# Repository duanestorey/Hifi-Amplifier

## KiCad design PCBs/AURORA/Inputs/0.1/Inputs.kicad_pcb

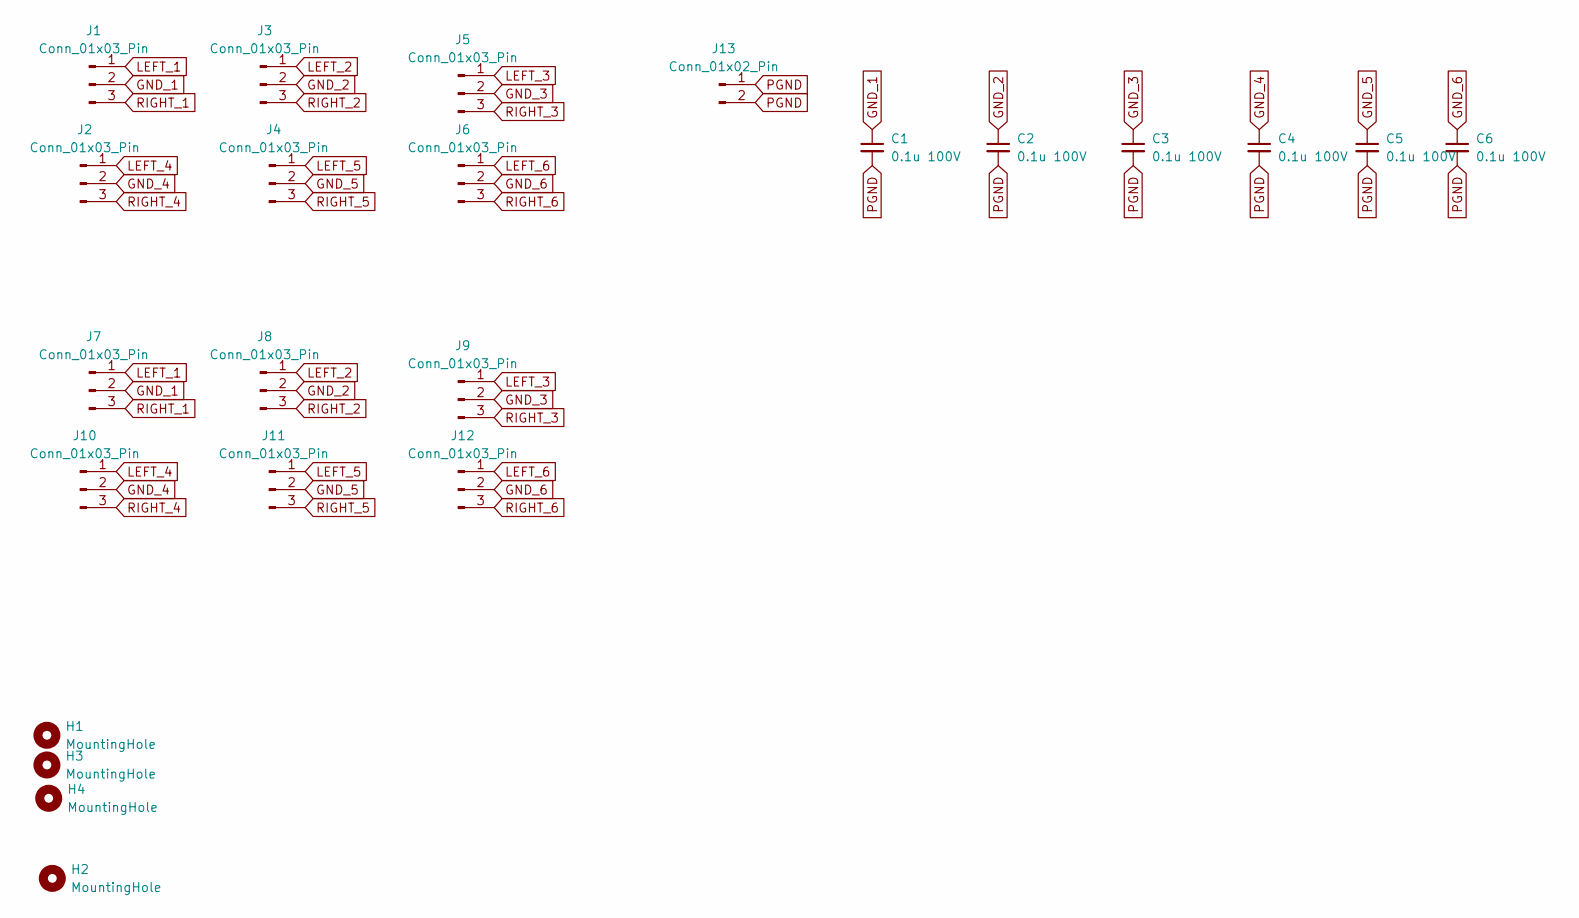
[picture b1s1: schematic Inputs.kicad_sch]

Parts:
C1, C2, C3, C4, C5, C6: 0.1u 100V; C_1206_3216Metric
H1, H2, H3, H4: MountingHole; MountingHole_3.2mm_M3
J1, J2, J3, J4, J5, J6, J7, J8, J9, J10, J11, J12: Conn_01x03_Pin; JST_PH_B3B-PH-K_1x03_P2.00mm_Vertical
J13: Conn_01x02_Pin; JST_VH_B2P-VH-B_1x02_P3.96mm_Vertical

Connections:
GND_1: C1.1, J1.2, J7.2
GND_2: C2.1, J3.2, J8.2
GND_3: C3.1, J5.2, J9.2
GND_4: C4.1, J2.2, J10.2
GND_5: C5.1, J4.2, J11.2
GND_6: C6.1, J6.2, J12.2
LEFT_1: J1.1, J7.1
LEFT_2: J3.1, J8.1
LEFT_3: J5.1, J9.1
LEFT_4: J2.1, J10.1
LEFT_5: J4.1, J11.1
LEFT_6: J6.1, J12.1
PGND: C1.2, C2.2, C3.2, C4.2, C5.2, C6.2, J13.1, J13.2
RIGHT_1: J1.3, J7.3
RIGHT_2: J3.3, J8.3
RIGHT_3: J5.3, J9.3
RIGHT_4: J2.3, J10.3
RIGHT_5: J4.3, J11.3
RIGHT_6: J6.3, J12.3

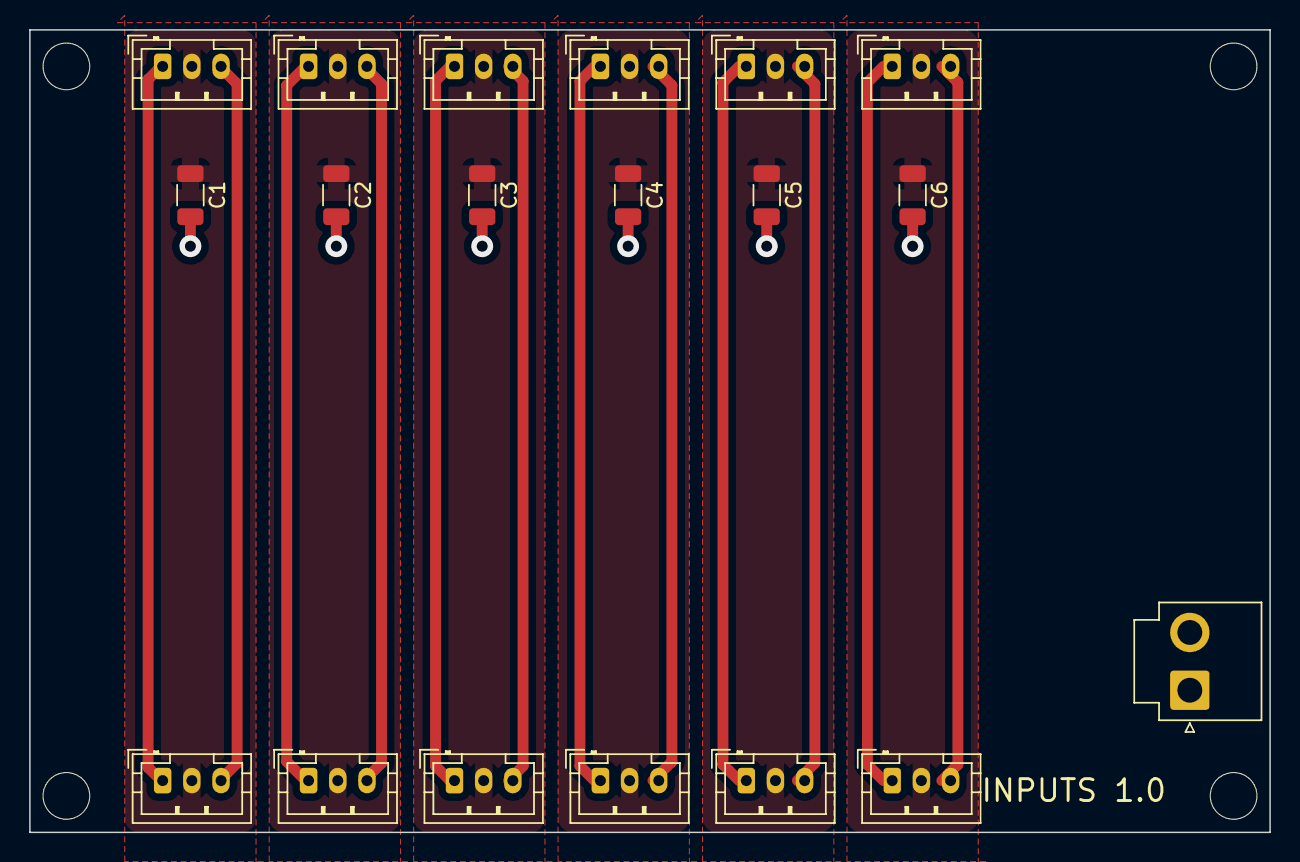
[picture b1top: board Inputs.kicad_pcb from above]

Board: 2 copper layers, 85.0 x 55.0 mm, 23 parts (0 on the bottom side), 19 nets.

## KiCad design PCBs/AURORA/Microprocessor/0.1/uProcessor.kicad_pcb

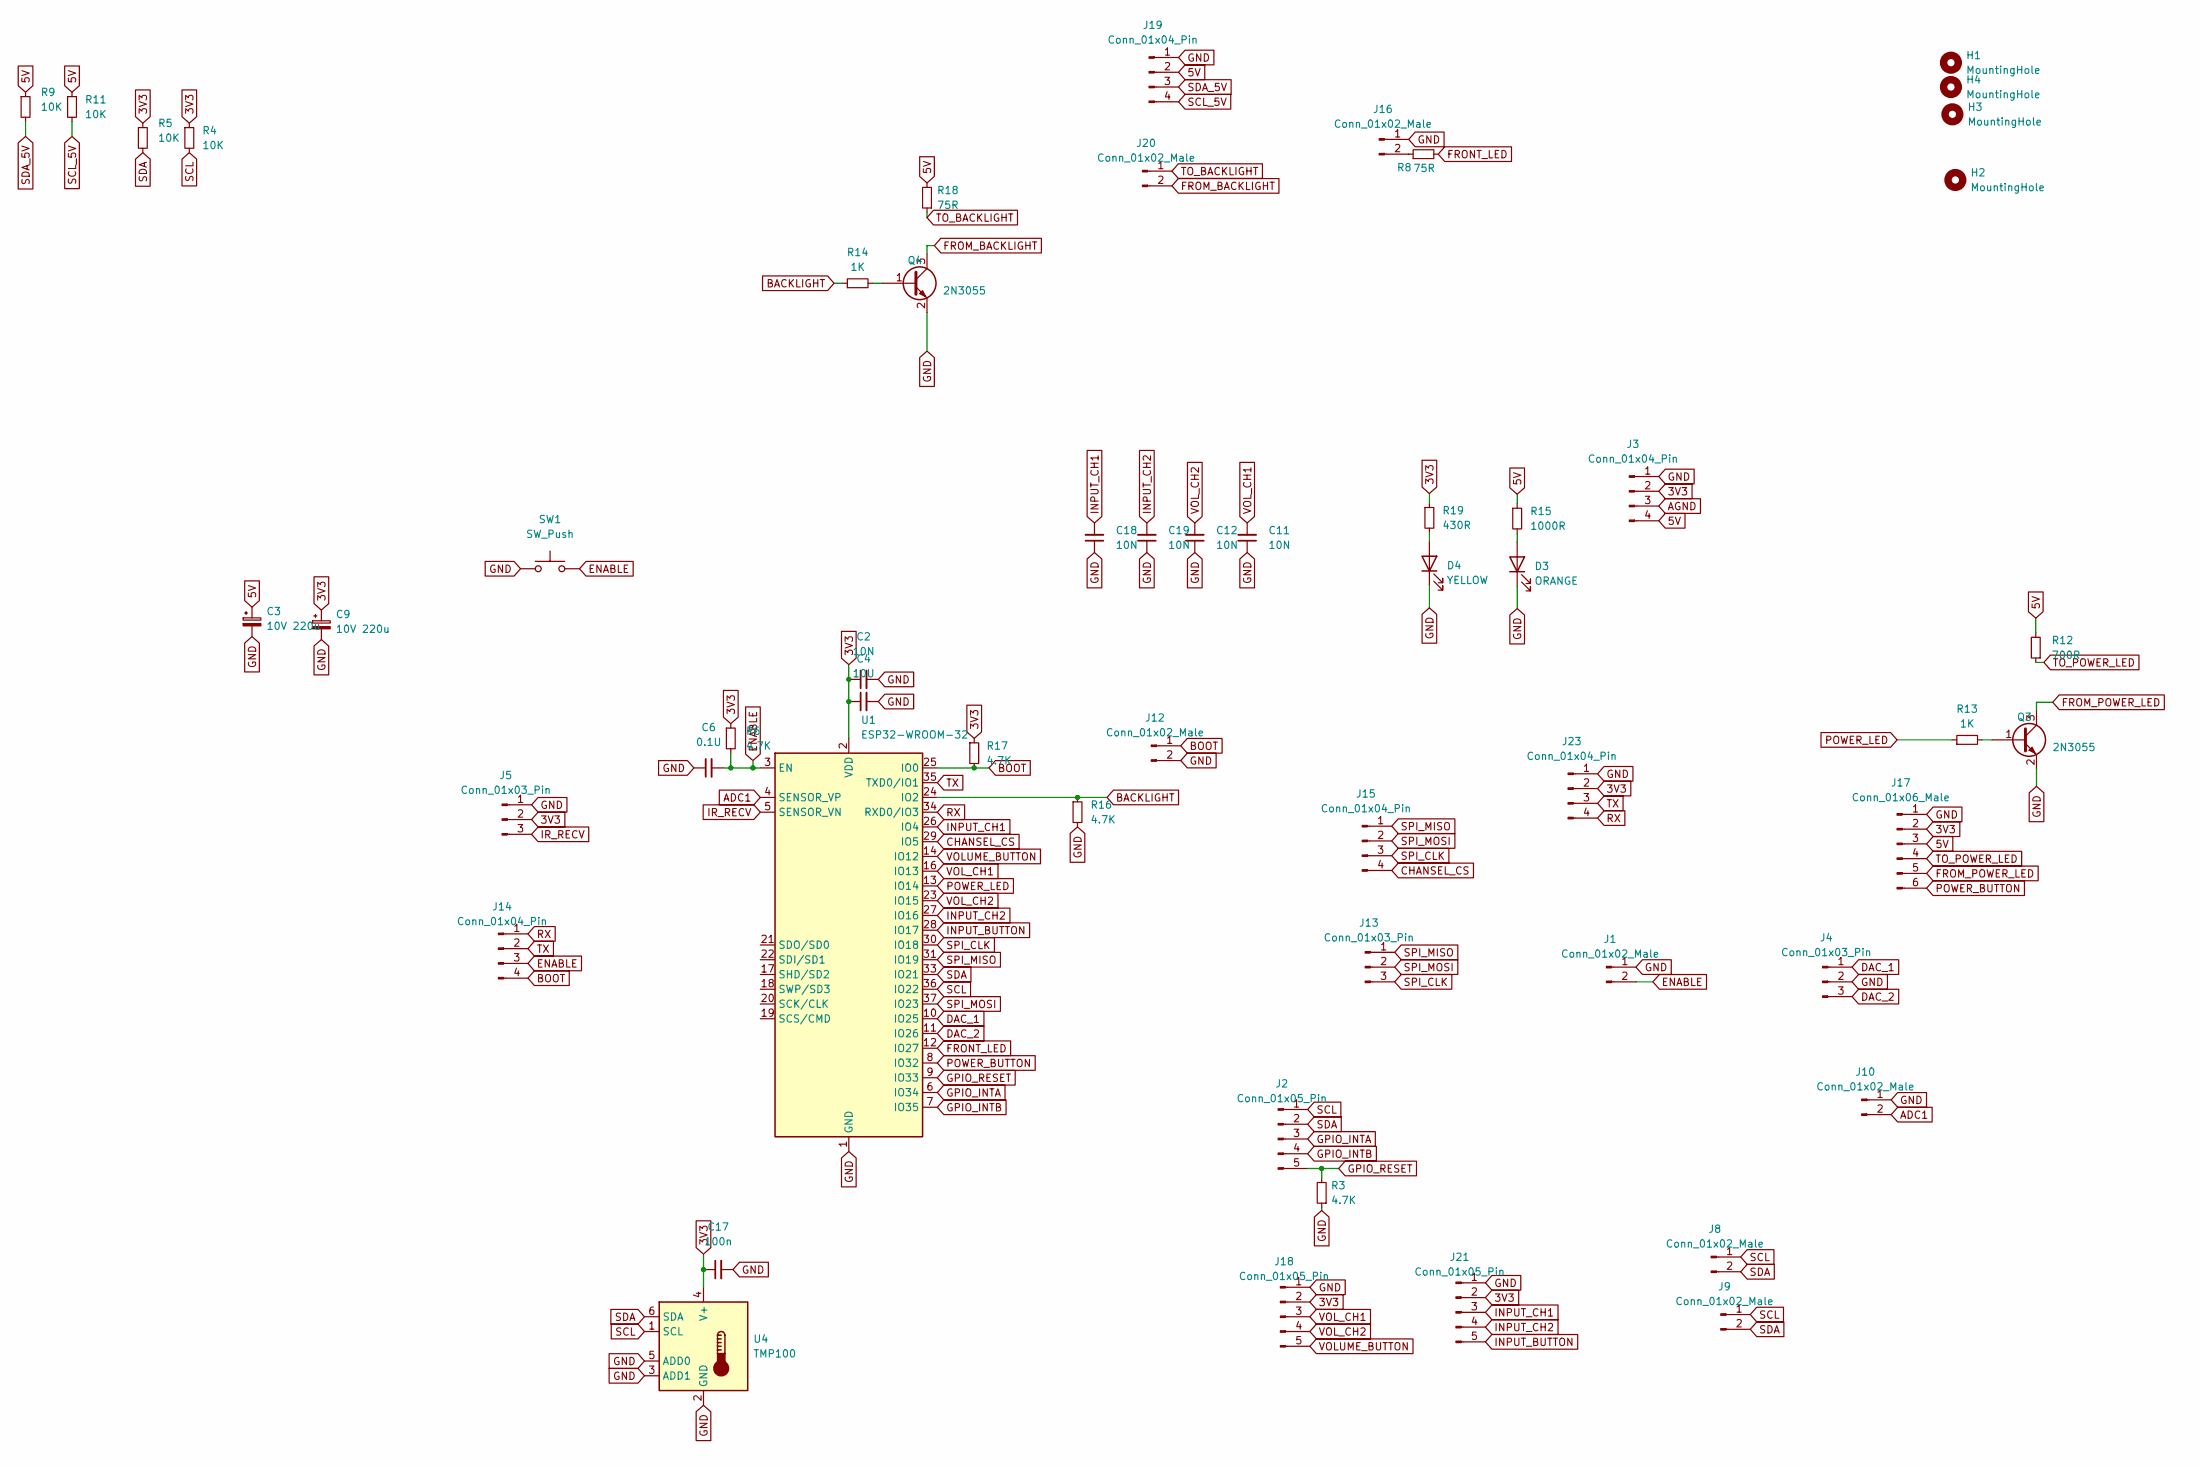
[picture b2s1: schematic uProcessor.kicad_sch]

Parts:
C2: 10N; C_0805_2012Metric_Pad1.18x1.45mm_HandSolder
C3, C9: 10V 220u; CP_Radial_D6.3mm_P2.50mm
C4: 10U; C_1206_3216Metric_Pad1.33x1.80mm_HandSolder
C6: 0.1U; C_0805_2012Metric_Pad1.18x1.45mm_HandSolder
C11, C12, C18, C19: 10N; C_0603_1608Metric_Pad1.08x0.95mm_HandSolder
C17: 100n; C_0805_2012Metric_Pad1.18x1.45mm_HandSolder
D3: ORANGE; LED_0805_2012Metric_Pad1.15x1.40mm_HandSolder; LCSC XL-1608UBC-04
D4: YELLOW; LED_0805_2012Metric_Pad1.15x1.40mm_HandSolder; LCSC NCD0603R1
H1, H2, H3, H4: MountingHole; MountingHole_3.2mm_M3
J1, J8, J9, J10, J16, J20: Conn_01x02_Male; JST_PH_B2B-PH-K_1x02_P2.00mm_Vertical
J2, J18, J21: Conn_01x05_Pin; JST_PH_B5B-PH-K_1x05_P2.00mm_Vertical
J3, J14, J15, J19: Conn_01x04_Pin; JST_PH_B4B-PH-K_1x04_P2.00mm_Vertical
J4, J5, J13: Conn_01x03_Pin; JST_PH_B3B-PH-K_1x03_P2.00mm_Vertical
J12: Conn_01x02_Male; PinHeader_1x02_P2.54mm_Vertical
J17: Conn_01x06_Male; JST_PH_B6B-PH-K_1x06_P2.00mm_Vertical
J23: Conn_01x04_Pin; PinHeader_1x04_P2.54mm_Vertical
Q3, Q4: 2N3055; TSOT-23
R3, R6, R16, R17: 4.7K; R_0603_1608Metric_Pad0.98x0.95mm_HandSolder
R4, R5, R9, R11: 10K; R_0603_1608Metric_Pad0.98x0.95mm_HandSolder
R8, R18: 75R; R_0603_1608Metric_Pad0.98x0.95mm_HandSolder
R12: 700R; R_0603_1608Metric_Pad0.98x0.95mm_HandSolder
R13, R14: 1K; R_0603_1608Metric_Pad0.98x0.95mm_HandSolder
R15: 1000R; R_0603_1608Metric_Pad0.98x0.95mm_HandSolder
R19: 430R; R_0603_1608Metric_Pad0.98x0.95mm_HandSolder
SW1: SW_Push; Button Aliexpress 4x4
U1: ESP32-WROOM-32; ESP32-WROOM-32E
U4: TMP100; SOT-23-6

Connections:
3V3: C2.1, C4.1, C9.1, C17.1, J3.2, J5.2, J17.2, J18.2, J21.2, J23.2, R4.1, R5.1, R6.1, R17.1, R19.1, U1.2 (VDD), U4.4 (V+)
5V: C3.1, J3.4, J17.3, J19.2, R9.1, R11.1, R12.2, R15.1, R18.2
ADC1: J10.2, U1.4 (SENSOR_VP)
AGND: J3.3
BACKLIGHT: R14.1, R16.1, U1.24 (IO2)
BOOT: J12.1, J14.4, R17.2, U1.25 (IO0)
CHANSEL_CS: J15.4, U1.29 (IO5)
DAC_1: J4.1, U1.10 (IO25)
DAC_2: J4.3, U1.11 (IO26)
ENABLE: C6.2, J1.2, J14.3, R6.2, SW1.2, U1.3 (EN)
FROM_BACKLIGHT: J20.2, Q4.3 (C)
FROM_POWER_LED: J17.5, Q3.3 (C)
FRONT_LED: R8.2, U1.12 (IO27)
GND: C2.2, C3.2, C4.2, C6.1, C9.2, C11.1, C12.1, C17.2, C18.1, C19.1, D3.1 (K), D4.1 (K), J1.1, J3.1, J4.2, J5.1, J10.1, J12.2, J16.1, J17.1, J18.1, J19.1, J21.1, J23.1, Q3.2 (E), Q4.2 (E), R3.1, R16.2, SW1.1, U1.1 (GND), U1.15 (GND), U1.38 (GND), U1.39 (GND), U4.2 (GND), U4.3 (ADD1), U4.5 (ADD0)
GPIO_INTA: J2.3, U1.6 (IO34)
GPIO_INTB: J2.4, U1.7 (IO35)
GPIO_RESET: J2.5, R3.2, U1.9 (IO33)
INPUT_BUTTON: J21.5, U1.28 (IO17)
INPUT_CH1: C18.2, J21.3, U1.26 (IO4)
INPUT_CH2: C19.2, J21.4, U1.27 (IO16)
IR_RECV: J5.3, U1.5 (SENSOR_VN)
unnamed: D3.2 (A), R15.2
unnamed: D4.2 (A), R19.2
unnamed: J16.2, R8.1
unnamed: Q3.1 (B), R13.2
unnamed: Q4.1 (B), R14.2
POWER_BUTTON: J17.6, U1.8 (IO32)
POWER_LED: R13.1, U1.13 (IO14)
RX: J14.1, J23.4, U1.34 (RXD0/IO3)
SCL: J2.1, J8.1, J9.1, R4.2, U1.36 (IO22), U4.1 (SCL)
SCL_5V: J19.4, R11.2
SDA: J2.2, J8.2, J9.2, R5.2, U1.33 (IO21), U4.6 (SDA)
SDA_5V: J19.3, R9.2
SPI_CLK: J13.3, J15.3, U1.30 (IO18)
SPI_MISO: J13.1, J15.1, U1.31 (IO19)
SPI_MOSI: J13.2, J15.2, U1.37 (IO23)
TO_BACKLIGHT: J20.1, R18.1
TO_POWER_LED: J17.4, R12.1
TX: J14.2, J23.3, U1.35 (TXD0/IO1)
VOLUME_BUTTON: J18.5, U1.14 (IO12)
VOL_CH1: C11.2, J18.3, U1.16 (IO13)
VOL_CH2: C12.2, J18.4, U1.23 (IO15)

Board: 2 copper layers, 55 parts (0 on the bottom side), 41 nets, no tracks yet.

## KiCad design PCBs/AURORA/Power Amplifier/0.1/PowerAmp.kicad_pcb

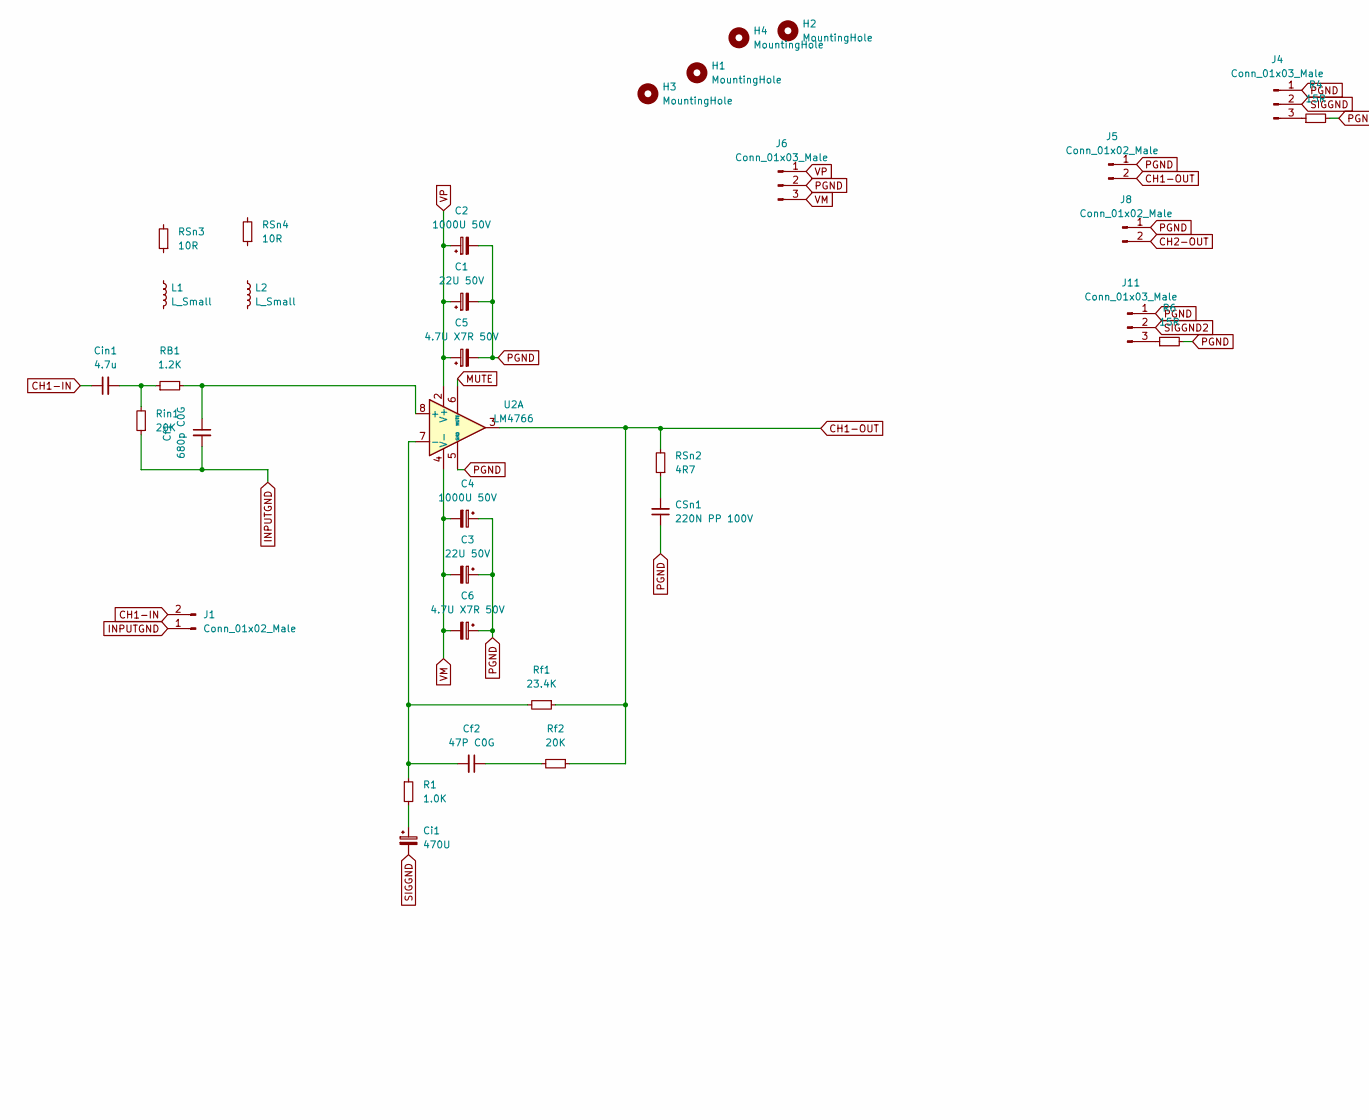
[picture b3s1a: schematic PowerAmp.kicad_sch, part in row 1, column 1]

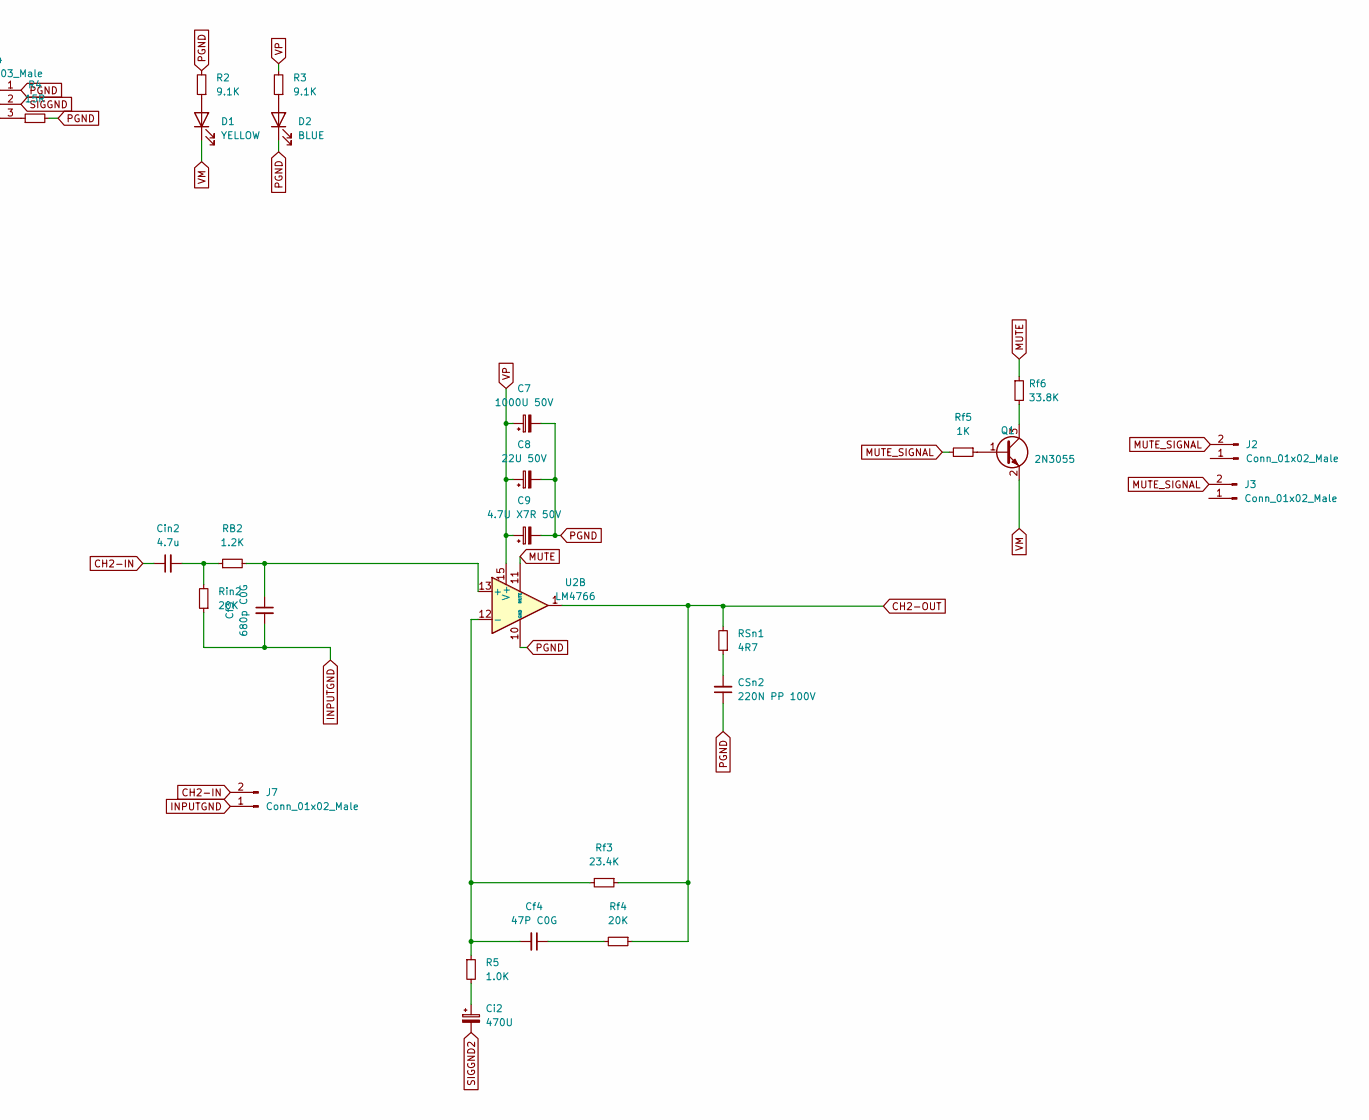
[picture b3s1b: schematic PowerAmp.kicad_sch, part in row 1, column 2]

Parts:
C1, C3, C8: 22U 50V; CP_Radial_D6.3mm_P2.50mm
C2, C4, C7: 1000U 50V; CP_Radial_D12.5mm_P5.00mm
C5, C6, C9: 4.7U X7R 50V; C_1206_3216Metric_Pad1.33x1.80mm_HandSolder
CSn1, CSn2: 220N PP 100V; C_Rect_L18.0mm_W7.0mm_P15.00mm_FKS3_FKP3
Cf1, Cf3: 680p C0G; C_1206_3216Metric_Pad1.33x1.80mm_HandSolder
Cf2, Cf4: 47P C0G; C_1206_3216Metric_Pad1.33x1.80mm_HandSolder
Ci1, Ci2: 470U; CP_Radial_D12.5mm_P5.00mm
Cin1, Cin2: 4.7u; 4.7uF Polypropylene Aliexpress
D1: YELLOW; LED_0805_2012Metric_Pad1.15x1.40mm_HandSolder
D2: BLUE; LED_0805_2012Metric_Pad1.15x1.40mm_HandSolder
H1, H2, H3, H4: MountingHole; MountingHole_3mm
J1, J2, J3, J7: Conn_01x02_Male; JST_PH_B2B-PH-K_1x02_P2.00mm_Vertical
J4, J11: Conn_01x03_Male; PinHeader_1x03_P2.54mm_Vertical
J5, J8: Conn_01x02_Male; JST_VH_B2P-VH_1x02_P3.96mm_Vertical
J6: Conn_01x03_Male; JST_VH_B3P-VH-B_1x03_P3.96mm_Vertical
L1, L2: L_Small; 500nH Inductor Aliexpress Air Gap
Q1: 2N3055; TSOT-23
R1, R5: 1.0K; R_1206_3216Metric_Pad1.30x1.75mm_HandSolder
R2, R3: 9.1K; R_0805_2012Metric_Pad1.20x1.40mm_HandSolder
R4, R6: 15R; R_0805_2012Metric_Pad1.20x1.40mm_HandSolder
RB1, RB2: 1.2K; R_1206_3216Metric_Pad1.30x1.75mm_HandSolder
RSn1, RSn2: 4R7; R_2512_6332Metric_Pad1.40x3.35mm_HandSolder
RSn3, RSn4: 10R; R_4020_10251Metric_Pad1.65x5.30mm_HandSolder
Rf1, Rf3: 23.4K; R_1206_3216Metric_Pad1.30x1.75mm_HandSolder
Rf2, Rf4: 20K; R_1206_3216Metric_Pad1.30x1.75mm_HandSolder
Rf5: 1K; R_0603_1608Metric_Pad0.98x0.95mm_HandSolder
Rf6: 33.8K; R_0603_1608Metric_Pad0.98x0.95mm_HandSolder
Rin1, Rin2: 20K; R_1206_3216Metric_Pad1.30x1.75mm_HandSolder
U2: LM4766; TO-220-15_P2.54x2.54mm_StaggerOdd_Lead4.58mm_Vertical

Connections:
CH1-IN: Cin1.1, J1.2
CH1-OUT: J5.2, RSn2.2, Rf1.1, Rf2.1, U2.3
CH2-IN: Cin2.1, J7.2
CH2-OUT: J8.2, RSn1.2, Rf3.1, Rf4.1, U2.1
INPUTGND: Cf1.2, Cf3.2, J1.1, J7.1, Rin1.1, Rin2.1
MUTE: Rf6.1, U2.6 (MUTE), U2.11 (MUTE)
MUTE_SIGNAL: J2.2, J3.2, Rf5.2
unnamed: CSn1.2, RSn2.1
unnamed: CSn2.2, RSn1.1
unnamed: Cf2.1, Rf2.2
unnamed: Cf4.1, Rf4.2
unnamed: Ci1.1, R1.2
unnamed: Ci2.1, R5.2
unnamed: Cin1.2, RB1.1, Rin1.2
unnamed: Cin2.2, RB2.1, Rin2.2
unnamed: D1.2 (A), R2.1
unnamed: D2.2 (A), R3.1
unnamed: J4.3, R4.1
unnamed: J11.3, R6.1
unnamed: Q1.1 (B), Rf5.1
unnamed: Q1.3 (C), Rf6.2
unnamed: Cf1.1, RB1.2, U2.8 (+)
unnamed: Cf2.2, R1.1, Rf1.2, U2.7 (-)
unnamed: Cf3.1, RB2.2, U2.13 (+)
unnamed: Cf4.2, R5.1, Rf3.2, U2.12 (-)
PGND: C1.2, C2.2, C3.1, C4.1, C5.2, C6.1, C7.2, C8.2, C9.2, CSn1.1, CSn2.1, D2.1 (K), J4.1, J5.1, J6.2, J8.1, J11.1, R2.2, R4.2, R6.2, U2.5 (GND), U2.10 (GND)
SIGGND: Ci1.2, J4.2
SIGGND2: Ci2.2, J11.2
VM: C3.2, C4.2, C6.2, D1.1 (K), J6.3, Q1.2 (E), U2.4 (V-)
VP: C1.1, C2.1, C5.1, C7.1, C8.1, C9.1, J6.1, R3.2, U2.2 (V+), U2.15 (V+)

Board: 4 copper layers, 58 parts (2 on the bottom side), 30 nets, no tracks yet.

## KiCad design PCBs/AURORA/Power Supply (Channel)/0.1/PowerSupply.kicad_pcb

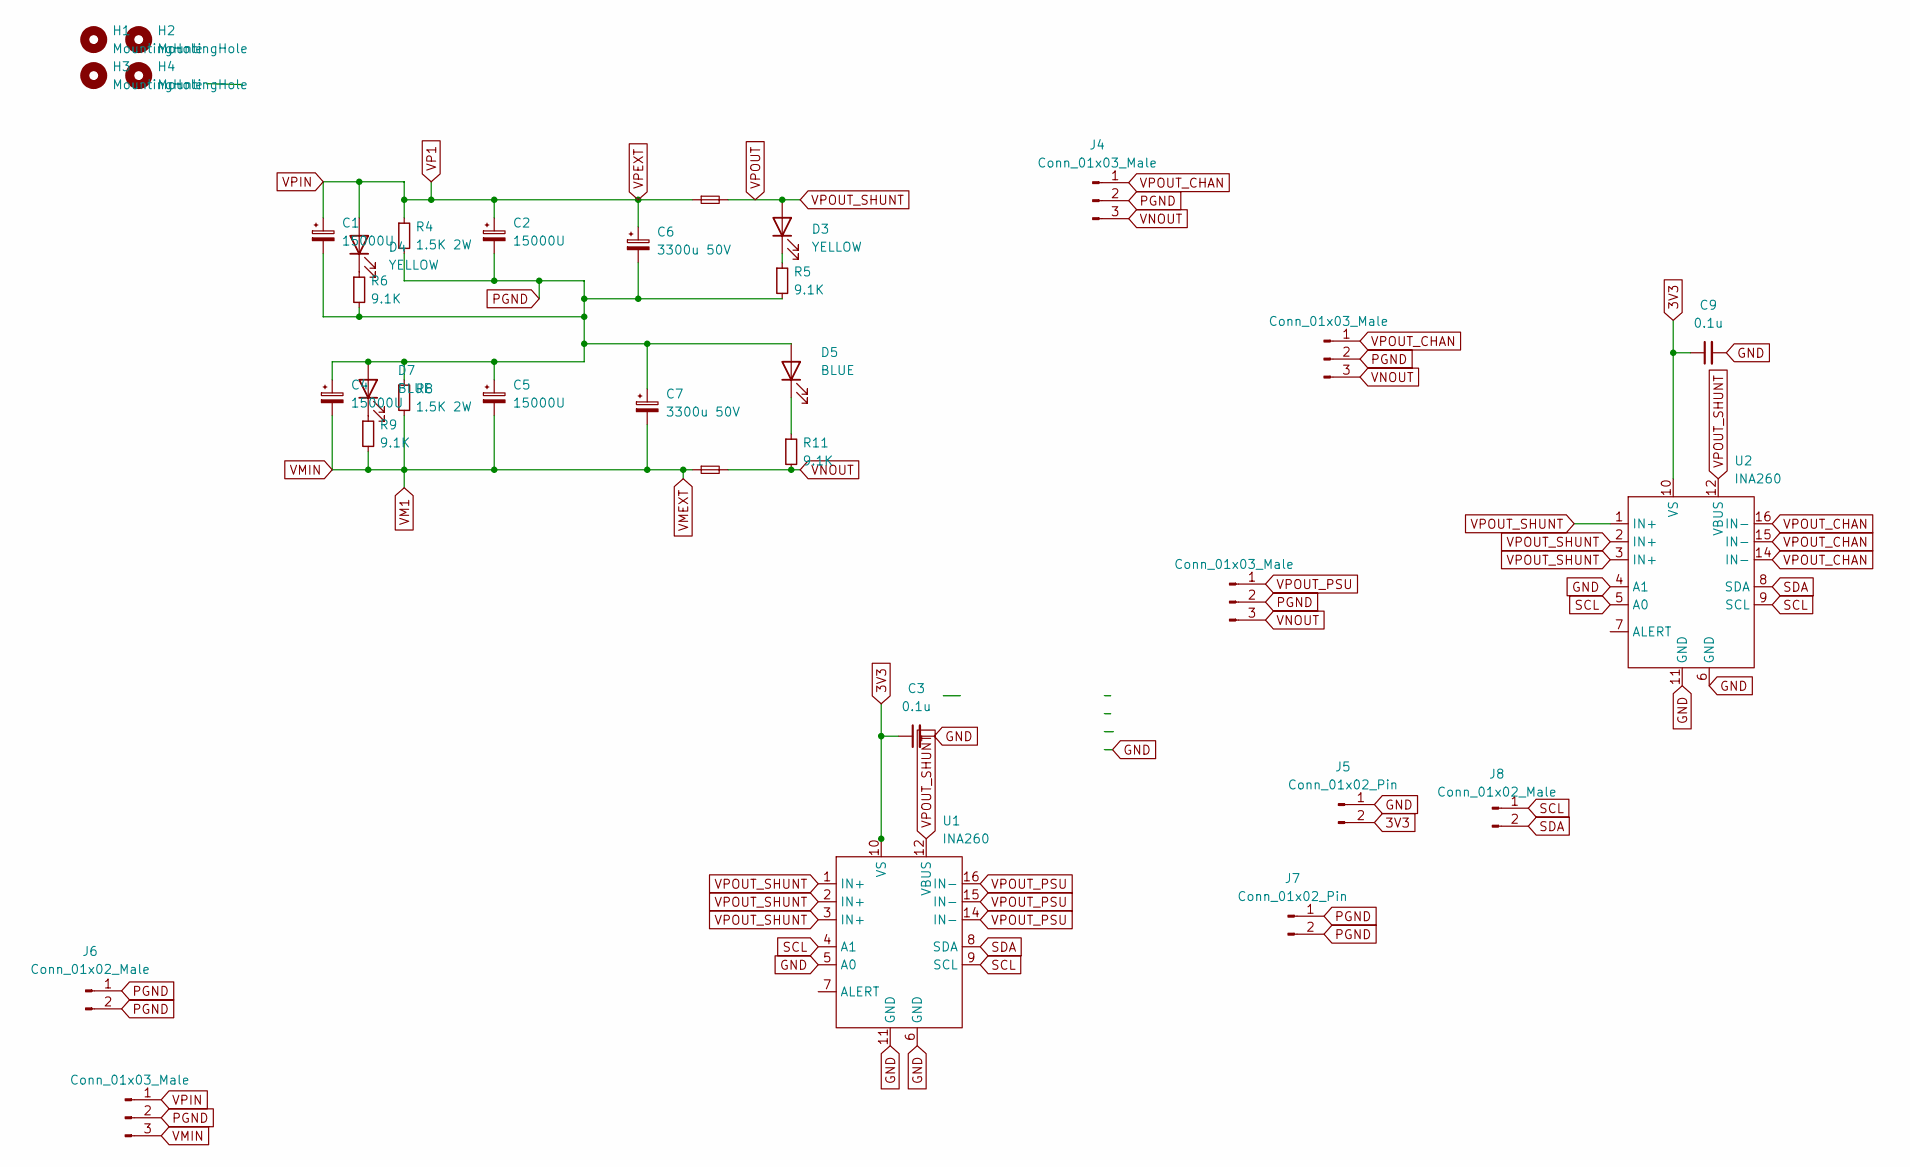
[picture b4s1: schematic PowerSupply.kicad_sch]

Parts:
C1, C2, C4, C5: 15000U; CP_Radial_D30.0mm_P10.00mm_SnapIn
C3, C9: 0.1u; C_0805_2012Metric_Pad1.18x1.45mm_HandSolder
C6, C7: 3300u 50V; CP_Radial_D18.0mm_P7.50mm
D3, D4: YELLOW; LED_0805_2012Metric_Pad1.15x1.40mm_HandSolder
D5, D7: BLUE; LED_0805_2012Metric_Pad1.15x1.40mm_HandSolder
F1, F2: Fuse_Small; Aliexpress Fuse 5x20
H1, H3: MountingHole; MountingHole_3mm
H2, H4: MountingHole; MountingHole_3.2mm_M3
J3, J4, J9, J10: Conn_01x03_Male; JST_VH_B3P-VH_1x03_P3.96mm_Vertical
J5, J7: Conn_01x02_Pin; JST_PH_B2B-PH-K_1x02_P2.00mm_Vertical
J6: Conn_01x02_Male; JST_VH_B2P-VH-B_1x02_P3.96mm_Vertical
J8: Conn_01x02_Male; JST_PH_B2B-PH-K_1x02_P2.00mm_Vertical
R4, R8: 1.5K 2W; R_2512_6332Metric_Pad1.40x3.35mm_HandSolder
R5, R6, R9, R11: 9.1K; R_0805_2012Metric_Pad1.20x1.40mm_HandSolder
U1, U2: INA260; TSSOP-16_4.4x5mm_P0.65mm

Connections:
3V3: C3.1, C9.1, J5.2, U1.10 (VS), U2.10 (VS)
GND: C3.2, C9.2, J5.1, U1.5 (A0), U1.6 (GND), U1.11 (GND), U2.4 (A1), U2.6 (GND), U2.11 (GND)
unnamed: D3.1 (K), R5.1
unnamed: D4.1 (K), R6.1
unnamed: D5.1 (K), R11.1
unnamed: D7.1 (K), R9.1
PGND: C1.2, C2.2, C4.1, C5.1, C6.2, C7.1, D5.2 (A), D7.2 (A), J3.2, J4.2, J6.1, J6.2, J7.1, J7.2, J9.2, J10.2, R4.2, R5.2, R6.2, R8.1
SCL: J8.1, U1.4 (A1), U1.9 (SCL), U2.5 (A0), U2.9 (SCL)
SDA: J8.2, U1.8 (SDA), U2.8 (SDA)
VM1: C4.2, C5.2, C7.2, F2.1, J9.3, R8.2, R9.2
VNOUT: F2.2, J3.3, J4.3, J10.3, R11.2
VP1: C1.1, C2.1, C6.1, D4.2 (A), F1.1, J9.1, R4.1
VPOUT: D3.2 (A), F1.2, U1.1 (IN+), U1.2 (IN+), U1.3 (IN+), U1.12 (VBUS), U2.1 (IN+), U2.2 (IN+), U2.3 (IN+), U2.12 (VBUS)
VPOUT_CHAN: J4.1, J10.1, U2.14 (IN-), U2.15 (IN-), U2.16 (IN-)
VPOUT_PSU: J3.1, U1.14 (IN-), U1.15 (IN-), U1.16 (IN-)

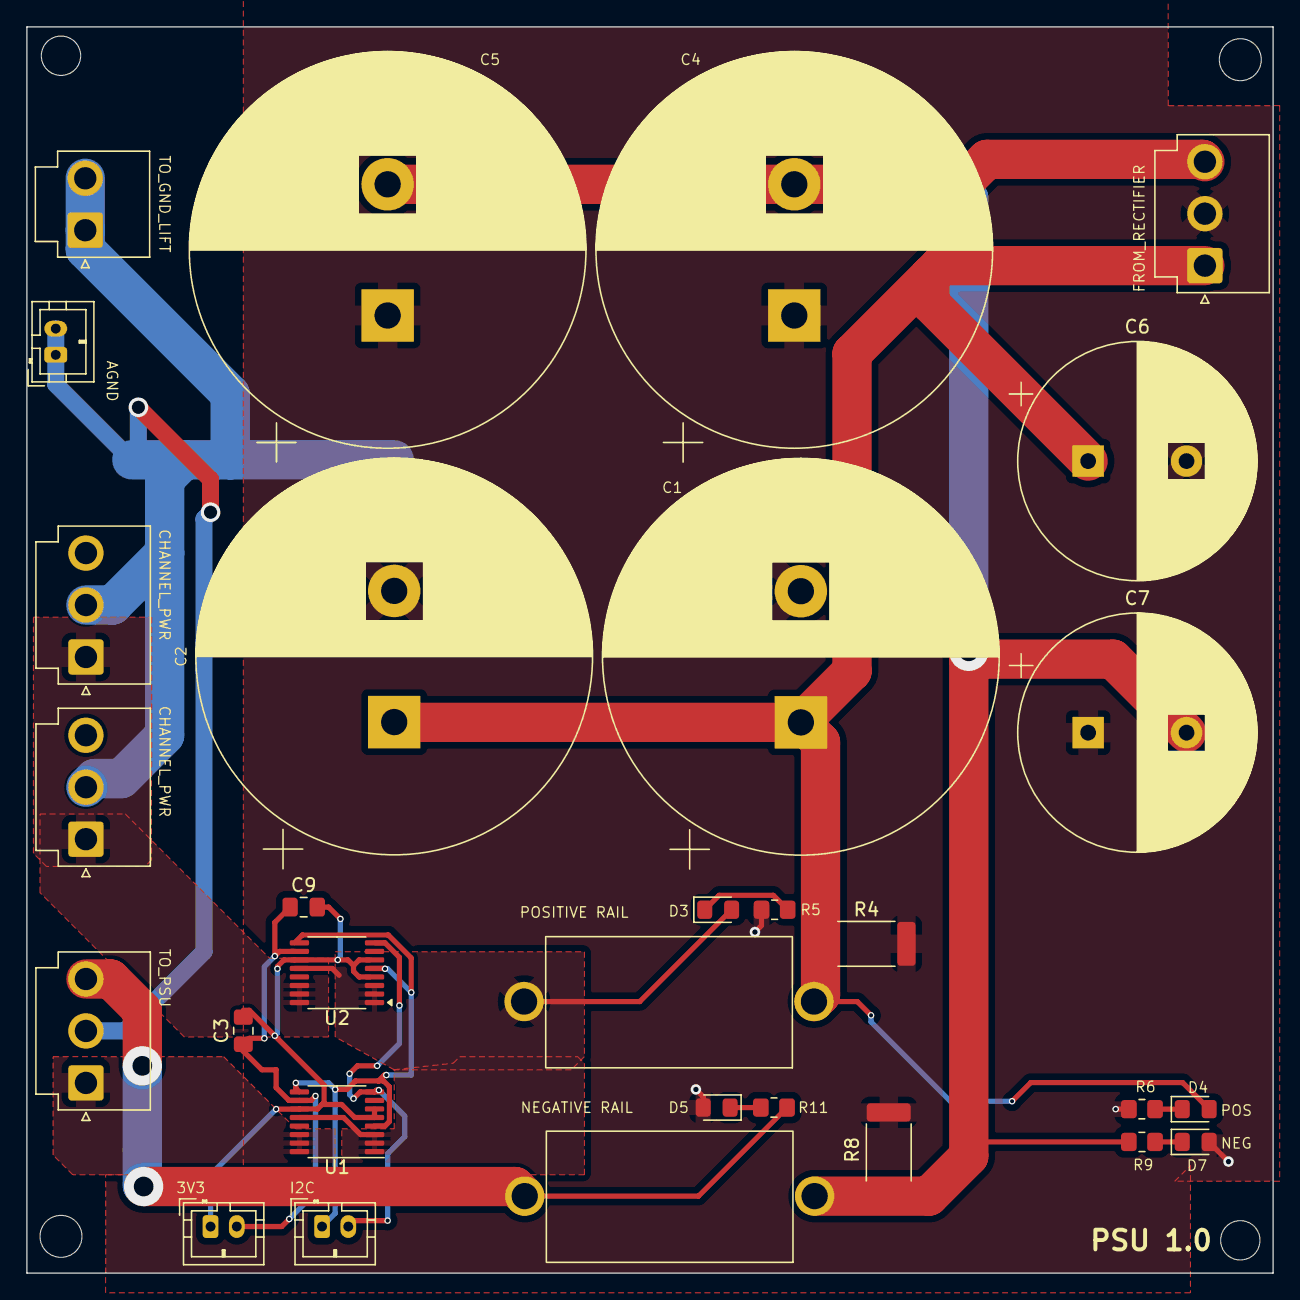
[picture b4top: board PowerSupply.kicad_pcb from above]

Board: 2 copper layers, 95.0 x 95.0 mm, 34 parts (0 on the bottom side), 15 nets.

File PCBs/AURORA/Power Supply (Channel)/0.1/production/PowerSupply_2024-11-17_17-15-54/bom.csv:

Designator,Footprint,Quantity,Value,LCSC Part #
"C1, C2, C4, C5",CP_Radial_D30.0mm_P10.00mm_SnapIn,4,15000U,
"D3, D4",0805,2,YELLOW,
"D5, D7",0805,2,BLUE,
"F1, F2",Aliexpress Fuse 5x20,2,Fuse_Small,
"H1, H3",MountingHole_3mm,2,MountingHole,
"H2, H4",MountingHole_3.2mm_M3,2,MountingHole,
"J1, J10, J2, J4, J9",JST_VH_B3P-VH_1x03_P3.96mm_Vertical,5,Conn_01x03_Male,
J7,JST_VH_B2P-VH-B_1x02_P3.96mm_Vertical,1,Conn_01x02_Male,
"R11, R5, R6, R9",0805,4,9.1K,
"R4, R8",R_Axial_DIN0414_L11.9mm_D4.5mm_P15.24mm_Horizontal,2,1.2K,
